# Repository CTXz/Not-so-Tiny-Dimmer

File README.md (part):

<!-- omit in toc -->
# Not-so-Tiny Dimmer 

What initaly just started as minimalist ATtiny based WS2812 LED strip dimmer, quickly turned into a cheap and feature rich ATtiny based WS2812 strip controller with single color, multi color and animation support. Non-addressable LED strips are also supported, but limited to single color features only.

## Contents
- [Contents](#contents)
- [Overview](#overview)
  - [Software](#software)
    - [Patches/Effects](#patcheseffects)
      - [`PATCH_SET_ALL`](#patchsetall)
      - [`PATCH_DISTRIBUTE`](#patchdistribute)
      - [`PATCH_ANIMATION_BREATHE_POT_CTRL`](#patchanimationbreathepotctrl)
      - [`PATCH_ANIMATION_BREATHE_RAND_POT_CTRL`](#patchanimationbreatherandpotctrl)
      - [`PATCH_ANIMATION_BREATHE_RAINBOW_POT_CTRL`](#patchanimationbreatherainbowpotctrl)
      - [`PATCH_ANIMATION_BREATHE_ARR_POT_CTRL`](#patchanimationbreathearrpotctrl)
      - [`PATCH_ANIMATION_RAINBOW`](#patchanimationrainbow)
      - [`PATCH_ANIMATION_RAINBOW_POT_CTRL`](#patchanimationrainbowpotctrl)
      - [`PATCH_ANIMATION_SWAP`](#patchanimationswap)
      - [`PATCH_ANIMATION_SWAP_POT_CTRL`](#patchanimationswappotctrl)
      - [`PATCH_ANIMATION_ROTATE_RAINBOW`](#patchanimationrotaterainbow)
      - [`PATCH_ANIMATION_RAIN`](#patchanimationrain)
      - [`PATCH_ANIMATION_RAIN_POT_CTRL`](#patchanimationrainpotctrl)
  - [Hardware](#hardware)
    - [Building](#building)
      - [Schematic](#schematic)
      - [PCBs](#pcbs)
        - [Showcase](#showcase)
        - [Ordering](#ordering)
        - [Soldering Tips](#soldering-tips)
      - [Perfboard](#perfboard)
      - [Showcase](#showcase-1)
- [Flashing the firmware](#flashing-the-firmware)
- [Credits](#credits)
- [Project log](#project-log)
- [License](#license)

## Overview

The Not-so-Tiny dimmer is a open source ATtiny Based WS2812 RGB strip controller that offers support for single and multi color lights, as well various animations. Alternatively, the controller can also be used to drive non-addressable LED strips, but is only limited to single color patches and animations. 

### Software

The controller offers a patch bank with up to 10 patches, where each patch slot can be hard-coded in the [configuration header](src/config.h) to something as simple as projecting a single color across the strip, all the way to projecting flashy rainbow animations. If less than 10 patches are desired, the `NUM_PATCHES` directive can be reduced in the [configuration header](src/config.h).

Non-addressable RGB strips are also supported by the firmware by changing the `STRIP_TYPE` configuration in the [configuration header](src/config.h) to `NON_ADDR`, but will limit the selection to single color patches. Whether a patch is supported on non-addressable strips is indicated in the comments of the [patch macro definitions](src/patch_macros.h). A [template configuration for non-addressable strips](src/config_templates/config_non-addressable.h) can be found in the [configuration_templates directory](src/config_templates/).

**Please note that the required amount of program flash rises with the number and complexity of patches. Thus, the use of an ATtiny25 is likely to only limited to a few single color patches.** For ATtiny25 based controllers, a [minimal configuration file template](src/config_templates/config_minimal.h) has been provided.

Due to the fact that patches are implemented C preprocessor directives, increasing the maximum number of patches requires addition of case statements in the [update_strip](https://github.com/CTXz/Tiny-Dimmer/blob/master/src/main.c#L193) function, along with a change of the `NUM_PATCHES` directive.

#### Patches/Effects

The following section lists all available patches that can be assigned to any of the 10 patch slots defined in the [configuration header](src/config.h):

##### `PATCH_SET_ALL`

Parameters:
|Type|Name|Description|
|----|----|-----------|
|`uint8_t`|R|Red value (0 - 255)|
|`uint8_t`|G|Green value (0 - 255)|
|`uint8_t`|B|Blue value (0 - 255)|

Description:

Sets the entire LED strip to one color. The brightness can be adjusted by the potentiometer.

Supported on non-addressable strips: Yes

Example:
```c
#define PATCH_0 PATCH_SET_ALL(255, 255, 255) // Fills strip with white
```

Showcase:

##### `PATCH_DISTRIBUTE`

Parameters:
|Type|Name|Description|
|----|----|-----------|
|`RGB_t[]`|RGB_ARR|An RGB_ARRAY() enclosed array of literal RGB arrays. Ex. `RGB_ARRAY({255, 255, 255}, {0, 1, 2}, ...)`|

Description:

Distributes the provided array of RGB values evenly accross the entire LED strip. The brightness can be adjusted by the potentiometer.

Supported on non-addressable strips: No

Example:

```c
// First strip half pink, second cyan
#define PATCH_0 PATCH_DISTRIBUTE ( \
        RGB_ARRAY (                \
                {10, 255, 202},    \
                {255, 20, 127}     \
        )                          \
)
```

Showcase:

##### `PATCH_ANIMATION_BREATHE_POT_CTRL`

Parameters:
|Type|Name|Description|
|----|----|-----------|
|`uint8_t`|R|Red value|
|`uint8_t`|G|Green value|
|`uint8_t`|B|Blue value|

Description:

"Breathes" the provided RGB value across the entire strip. The duration of a "breath" can be altered by the potentiometer.

Supported on non-addressable strips: Yes

Example:

```c
#define PATCH_0 PATCH_ANIMATION_BREATHE_POT_CTRL(255, 255, 255) // Breathes white color
```

Showcase:

##### `PATCH_ANIMATION_BREATHE_RAND_POT_CTRL`

Description:

"Breathes" random RGB values across the entire strip.
The duration of the "breath" can be altered by the potentiometer.
Due to the rather poor randomness of rand(), the outcomes tend
to be similar.

Supported on non-addressable strips: Yes

Example:
```c
#define PATCH_0 PATCH_ANIMATION_BREATHE_RAND_POT_CTRL
```

##### `PATCH_ANIMATION_BREATHE_RAINBOW_POT_CTRL`

Parameters:

|Type|Name|Description|
|----|----|-----------|
|`uint8_t`|RGB_STEP_SIZE|Color steps after every "breath". A greater step size means the color difference  between each breath becomes more noticeable.|

Description:
c
Gradiently "Breathes" trough the rgb spectrum. The duration of the "breath" can be altered by the potentiometer.

Supported on non-addressable strips: Yes

Example:
```c
#define PATCH_0 PATCH_ANIMATION_BREATHE_RAINBOW_POT_CTRL(10) // Breathes trough rainbow with 10 steps in color between each breath
```

##### `PATCH_ANIMATION_BREATHE_ARR_POT_CTRL`

Parameters:

|Type|Name|Description|
|----|----|-----------|
|`RGB_t[]`|RGB_ARR|An RGB_ARRAY() enclosed array of literal RGB arrays, ex. RGB_ARRAY({255, 255, 255}, {0, 1, 2}, ...)|

Description:

Gradiently "Breathes" trough the RGB array. The duration of the "breath" can be altered by the potentiometer.

Supported on non-addressable strips: Yes

Example:
```c
// Breathes trough red, green and blue
#define PATCH_0 PATCH_ANIMATION_BREATHE_ARR_POT_CTRL ( \
        RGB_ARRAY (                                    \
                {255, 0, 0},                           \
                {0, 255, 0},                           \
                {0, 0, 255}                            \
        )                                              \
)
```

##### `PATCH_ANIMATION_RAINBOW`

Parameters:

|Type|Name|Description|
|----|----|-----------|
|`uint8_t`|STEP_SIZE|Color steps (0 - 255) between each call. A greater value results in faster fading.|

Description:

Gradiently fades all LEDs simultaneously trough the RGB spectrum.

Supported on non-addressable strips: Yes

Example:
```c
#define PATCH_0 PATCH_ANIMATION_RAINBOW(10) // Fade trough RGB spectrum with 10 steps between each color change
```

Showcase:

##### `PATCH_ANIMATION_RAINBOW_POT_CTRL`

Description:

Gradiently fades all LEDs simultaneously trough the RGB spectrum.
The step size, and thus fade speed, can be altered by the potentiometer.

Supported on non-addressable strips: Yes

Example:

```c
#define PATCH_0 PATCH_ANIMATION_RAINBOW_POT_CTRL
```

##### `PATCH_ANIMATION_SWAP`

Parameters:

|Type|Name|Description|
|----|----|-----------|
|`uint8_t`|RFH|Red value of first strip half|
|`uint8_t`|GFH|Green value of first strip half|
|`uint8_t`|BFH|Blue value of first strip half|
|`uint8_t`|RFH|Red value of second strip half|
|`uint8_t`|GFH|Green value of second strip half|
|`uint8_t`|BFH|Blue value of second strip half|
|`unsigned long`|SWAP_TIME|Time (ms) after which the halves get swapped|

Description:

Splits the strip in two halves and continuously swaps their colors.

Supported on non-addressable strips: No

Example:
```c
#define PATCH_9 PATCH_ANIMATION_SWAP(255, 0, 0, 0, 0, 255, 1000) // Swaps between off and a random color
```

Showcase:

##### `PATCH_ANIMATION_SWAP_POT_CTRL`

Parameters:

|Type|Name|Description|
|----|----|-----------|
|`uint8_t`|RFH|Red value of first strip half|
|`uint8_t`|GFH|Green value of first strip half|
|`uint8_t`|BFH|Blue value of first strip half|
|`uint8_t`|RFH|Red value of second strip half|
|`uint8_t`|GFH|Green value of second strip half|
|`uint8_t`|BFH|Blue value of second strip half|

Description:

Splits the strip in two halves and continuously swaps their colors. The swap time can be altered by the potentiometer.

Supported on non-addressable strips: No

```c
#define PATCH_9 PATCH_ANIMATION_SWAP(255, 0, 0, 0, 0, 255) // Swaps between red and blue at a speed set by the potentiometer
```

##### `PATCH_ANIMATION_ROTATE_RAINBOW`

Parameters:

|Type|Name|Description|
|----|----|-----------|
|`uint8_t`|step_size|Color steps between each pixel|

Description:

Rotates the rgb spectrum across the strip.

Example:
```c
#define PATCH_0 PATCH_ANIMATION_ROTATE_RAINBOW(10)
```

Supported on non-addressable strips: No

Showcase:

##### `PATCH_ANIMATION_RAIN`

Parameters:

|Type|Name|Description|
|----|----|-----------|
|`uint8_t`|_R|Red color value|
|`uint8_t`|_G|Green color value|
|`uint8_t`|_B|Blue color value|
|`uint16_t`|MAX_DROPS|Maximum amount of visible "droplets" at a time|
|`uint16_t`|MIN_T_APPART|Minimum time in ms between drops|
|`uint16_t`|MAX_T_APPART|Maximum time in ms between drops|
|`uint8_t`|STEP_SIZE|Step size of droplet fading|

Description:

Creates a rain effect across the strip.
Note that this effect makes use of an RGB buffer and will linearly increase memory consumption with strip size.

Supported on non-addressable strips: No

Example:

```c
// White and cyan rain with max 10 drops, a minimum time of 0ms, maximum time of 100ms and step size of 10
#define PATCH_0 PATCH_ANIMATION_RAIN(255, 255, rand()%255, 10, 0, 100, 10)
```

Showcase:

##### `PATCH_ANIMATION_RAIN_POT_CTRL`

Parameters:

|Type|Name|Description|
|----|----|-----------|
|`uint8_t`|_R|Red color value|
|`uint8_t`|_G|Green color value|
|`uint8_t`|_B|Blue color value|

Description:

Creates a rain effect across the strip. The "intensity" of the rain can be adjusted with the potentiometer. Note that this effect makes use of an RGB buffer and will linearly increase memory consumption with strip size.

Supported on non-addressable strips: No

Example:

```c
// White and cyan rain with potentiometer intensity control
#define PATCH_0 PATCH_ANIMATION_RAIN(255, 255, rand()%255)
```

### Hardware

To navigate trough the patch bank, a single push button is provided. Once the last patch has been reached, the first patch is loaded again upon button press. Many patches also offer a tweakable parameter, such as brightness and speed control. A potentiometer is used to adjust these parameters in real time.

To compensate for sloppy hardware jobs, the firmware also offers potentiometer and push button noise reduction to reduce brightness flickering and false patch toggling. It should be noted however, that these features cost program flash and runtime cycles and can be adjusted or disabled in the [configuration header](src/config.h).

The controller firmware has been written for ATtiny85 chips, but will tightly fit onto a ATtiny25 chip if fewer and minimal patches are used. Unless the controller is planned to be used as a simple single-color WS2812 RGB dimmer, it is really recommended to at least use an ATiny45, preferably an ATiny85 if one wants make full use of all features.

#### Building

The schematics and PCB files, including the gerbers, for the WS2812 and non-addressable LED strips versions can be found here:

- [WS2812](kicad/Not-So-Tiny-Dimmer/)
- [Non-Addressable strips](kicad/Not-So-Tiny-Dimmer_Non-addr/)

Alternatively, one can also build the Tiny Dimmer on a perfboard. A perfboard layout diagram for the WS2812 version has been provided in the [perfboard section)(#Perfboard) bellow.

The following components are required to build a Not-so-Tiny dimmer for WS2812 strips:

|Component|Quantity|Description|
|---------|--------|-----------|
|WS2812 strip|1|The controller drives addressable WS2812 RGB strips.|
|ATtiny 85/45/25|1|The chip that runs the firmware, hence the name "Tiny" in the name. Although the firmware will barely fit on a ATtiny25, it is highly recommended to use an ATiny45 or ATiny85 if additional features are to be added to the software later.|
|10k - 100k resistor (0204 recommended)|1|Pulls up the reset pin to prevent random resets (Optional for extra stability, since the ATtiny already has an internal pull-up)|
|1k resistor (0204 recommended)|1|Optional, used, along wiht a 100nf cermaic cap, to reduce push button debouncing|
|10k **vertical** linear potentiometer ([example](https://tech.alpsalpine.com/prod/e/html/potentiometer/rotarypotentiometers/rk09k/rk09k_list.html))|1|Used to set the brightness. 10k linear pots are recommended, but any linear pot between 1k and 100k should do the job.|
|10uF Electrolytic Capacitor|1|Optional, but helps decoupling power supply noise.|
|100nF Ceramic Capacitor|2|Optional, used to decouple supply noise and reduce push button debouncing|
|6mm x 6mm x (7mm - 10mm) Tactile Push Button|1|Used to toggle between colors and to activate fading. A height of at least 7mm is recommended.|
|2.54mm Male/Female headers|1|SPI header to program the MCU.|
|2.54mm 3 Pin PCB screw terminal block|1|WS2812 connector.|
|DC Barrel Jack|1|5V Voltage supply input.|

For a non-addressable strip controller, the following parts are requried:

|Component|Quantity|Description|
|---------|--------|-----------|
|Non-Addressable RGB strip|1|The controller drives non addressable RGB strips.|
|ATtiny 85/45/25|1|The chip that runs the firmware, hence the name "Tiny" in the name. Although the firmware will barely fit on a ATtiny25, it is highly recommended to use an ATiny45 or ATiny85 if additional features are to be added to the software later.|
|10k - 100k resistor|1|Pulls up the reset pin to prevent random resets (Optional for extra stability, since the ATtiny already has an internal pull-up)|
|1k resistor|1|Optional, used, along wiht a 100nf cermaic cap, to reduce push button debouncing|
|10k **vertical** linear potentiometer ([example](https://tech.alpsalpine.com/prod/e/html/potentiometer/rotarypotentiometers/rk09k/rk09k_list.html))|1|Used to set the brightness. 10k linear pots are recommended, but any linear pot between 1k and 100k should do the job.|
|10uF Electrolytic Capacitor|1|Optional, but helps decoupling power supply noise.|
|100nF Ceramic Capacitor|2|Optional, used to decouple supply noise and reduce push button debouncing|
|6mm x 6mm x (7mm - 10mm) Tactile Push Button|1|Used to toggle between colors and to activate fading. A height of at least 7mm is recommended.|
|IRF630 N-MOS|3|Drives the 12V powered RGB strip. Most TO-220 N-MOSFETs with the same pinout will do.|
|2.54mm Male/Female headers|1|SPI header to program the MCU.|
|2.54mm 2 Pin PCB screw terminal block|2|12V, 5V and GND Voltage supply input.|
|2.54mm 4 Pin PCB screw terminal block|1|Non-Addressable strip connector.|

The controller can also be easily be built with a digispark board. 

The price for the components can range anywhere between 10 to 15 EUR, depending from where you purchase the components, and their quality.

##### Schematic

WS2812 Version: 

Non-Addressable strip version:

##### PCBs

WS2812 Version:

Non-Addressable strip version:

###### Showcase

PCB rev 1.0.0 (hence the few quirks) front showcase:

PCB rev 1.0.0 back showcase (pardon the solder flux):

###### Ordering

To order PCBs, simply send the gerber files (found under the `kicad/` directory) to your favorite PCB manufacturer. For my boards, I have chosen to order them from [JLCPCB](https://jlcpcb.com/?gclid=Cj0KCQjwncT1BRDhARIsAOQF9LkeNfO6bdbyJwIi-upbhMTT3J_9f7ANeXa-8HaEN9GSgqXFjCqWPz4aAvFlEALw_wcB).

###### Soldering Tips

Some tips when soldering the PCBs:

- The push button and potentiometer are soldered to the back side of the PCB. This is so that the PCB can be easily mounted onto a panel.
- Start with the small components (resistors, ceramic caps)
- Some vertical pots have too big mounting pins (pins on the side) for the PCB. Cutting the mounting pins short does the job.

##### Perfboard

Top view:

##### Showcase

Perfboard:

## Flashing the firmware

Flashing the firmware is possible even with the chips attached to the board. Hence it is recommended to solder an SPI header onto the board if you're planning to update the software and do not wish to open up the device for every firmware update.

To flash the firmware, an SPI programmer is required. Since I still have a few spare Arduino's lying around, I decided to use an Arduino Leonardo with the [Arduino ISP firmware](https://www.arduino.cc/en/tutorial/arduinoISP) installed to program the controller.

Programming via SPI with ArduinoISP:

Since the firmware has been written in [PlatformIO](https://platformio.org/), it is easiest to download the IDE, simply import the project and flash it from there.

Should your Not-so-Tiny dimmer not use an ATtiny85, you must change the `board` directive in the [PlatformIO configuration file](platformio.ini) to your ATtiny model.   

In addition to that, the [PlatformIO configuration file](platformio.ini) also expects a stk500v1 programmer (compatible with Arduino over ISP). If you are not programming the controller via an Arduino, you must change `upload_protocol` to the the corresponding programmer in the configuration file (See the [PlatformIO atemlavr documentation](https://docs.platformio.org/en/latest/platforms/atmelavr.html)).

Once everything is set in PlatformIO, make sure the parameters in the [configuration header](src/config.h) match your needs and simply click the upload button. The firmware should be flashed onto your controller in no time. 

If you're planning to flash the firmware without the PlatformIO IDE, **make sure to program the ATtiny's fuses for it to run at 16Mhz!**

## Credits

Big credits to @cpldcpu's [light_ws2812](https://github.com/cpldcpu/light_ws2812) library as plenty of hise code has been used to drive the WS2812 strip.

## Project log

The Tiny dimmer was built mostly out of necessity for a kitchen light and quarantine boredom. The choice of components was initially more or less a result of the limited number of spare parts that I had lying around at home. In particular, I had a digispark with an ATtiny25 soldered onto it, which I figured could suffice for a simple kitchen light.
Working with 2 KB of program flash and 128 B of RAM certainly came with its challenges. The tiny amount of program memory put the use of the Arduino library and the common NeoPixelBus library completely out of question and I was forced to write the code in pure AVR C.

To drive the WS2812 strip I decided to give [cpldcpu's light_ws2812](https://github.com/cpldcpu/light_ws2812) library a shot, which I had essentially stripped down to the `ws2812_sendarray_mask` function. Since my plan was to control all pixels of the strip simultaneously (yes, I'm aware I could've used non addressable strips for that, but WS2812 strips are all I have lying around... besides they just need one pin to be driven), I had to find a way to alter the `ws2812_sendarray_mask` function to no longer accept a pixel buffer, which wastes an enormous amount of RAM, but rather a RGB object which it would apply to all LEDs.

Easier said than done, as the function is incredibly time sensitive. That's the  reason as to why the `ws2812_sendarray_mask` function's main loop, which transmits the color data to the strip, has been written in AVR assembly (unfortunately a assembly languages that I'm still very unfamiliar with). Applying the slightest changes always ended up breaking the function, until I figured that the compiler optimization might be the reason behind that. Turns out, by turning the compiler optimization using the `#pragma GCC pop_options` macro, the main loop becomes allot less sensitive to changes. I haven't taken a look at the pulse time differences that arise with and without optimization enabled, but it might be something interesting to look into. Never the less, I was happy that I could finally control the WS2812 strip as desired, without blowing away the ATtinys 128 B of RAM, and thus I rewrote the `ws2812_send_array` function to `ws2812_set_all` which sets all pixels to a provided RGB value.

From here, implementing the firmware was rather straight forward. Initially I planned to assign the push button an INT0 interrupt. However, after implementing button hold detection and noise reduction, support for interrupts has been dropped in favour of a pure state polling implementation.

Adding the fade animation was a little tricky in that its maximum speed, provided its best resolution, was heavily limited by the speed of the `ws2812_set_all` function. Hence, for faster fading speeds, I was forced to increase the step size for the colors, meaning faster fading speeds come at the cost of smoothness/resolution.

All in all, this was a fun project to kill some quarantine time and most importantly, I'm more than happy with the way the result turned out and it was nice to put my AVR C skills to use again. Sure, I could've bought a cheap chinese LED strip controller, but where's the fun in that. This controller is all about open source and allows me to extend its features by reprogramming it. If I ever plan on discarding it, I can simply pop out and desolder all components are reuse them for another project.

--- Update ---

I have since reworked the software quite a bit. The ws2812 functions have been reduced to a set of 4 core functions, `ws2812_prep_tx()`, `ws2812_wait_rst()`, `ws2812_tx_byte()`, `ws2812_end_tx()`. With these functions I have then implemented a hardware abstraction layer in the [strip.c](src/strip.c) file, which defines various routines to control the LED strip. Patches have been completely reworked and are now defined in the [configuration header](src/config.h) using macros provided by the [patch_macros.h](src/patch_macros.h) header file. Using macros allows for very flexible patches that aren't limited to a single function or some sort of array of a specific data type. This made room for the easy implementation of animations.

--- Update ---

I think it's time to admit that this project is no longer a minimal dimmer, in fact, it has become quite the opposite and is turning into a feature bloated over-engineered ATtiny based WS2812 controller that, at least if the quarantine boredom won't end soon, will be connected, and will require connection, to the world wide web, feature the clunkiest most inaccurate and unnecessary voice control, feature incredibly water and dust sensitive touch controls and some form of AI or who knows what the future offers.

In all seriousness, except for the fact that I've now renamed the project to Not-so-Tiny dimmer, the device can now be more accurately considered a LED strip controller. While I personally do take large joy in adding and using the additional flashy animations, I've taken into account that we're starting to cross the RGB hell border in the eyes of many people, and have hence made sure that the software architecture is very flexible and allows one to take full control of which features and patches to be implemented. Hell, if desired, the controller software can be reduced to only support a single light setting along with brightness control.

## License

All code in this project is licensed by the GNU GPLv3 license and hardware is licensed by the [TAPR Open Hardware License](https://tapr.org/the-tapr-open-hardware-license/).

Both licenses require to provide a copy of the modified source code and/or hardware documentation for any derivative work.

GNU GPLv3
```
                    GNU GENERAL PUBLIC LICENSE
                       Version 3, 29 June 2007

 Copyright (C) 2007 Free Software Foundation, Inc. <https://fsf.org/>
 Everyone is permitted to copy and distribute verbatim copies
 of this license document, but changing it is not allowed.

                            Preamble

  The GNU General Public License is a free, copyleft license for
software and other kinds of works.

  The licenses for most software and other practical works are designed
to take away your freedom to share and change the works.  By contrast,
the GNU General Public License is intended to guarantee your freedom to
share and change all versions of a program--to make sure it remains free
software for all its users.  We, the Free Software Foundation, use the
GNU General Public License for most of our software; it applies also to
any other work released this way by its authors.  You can apply it to
your programs, too.

  When we speak of free software, we are referring to freedom, not
price.  Our General Public Licenses are designed to make sure that you
have the freedom to distribute copies of free software (and charge for
them if you wish), that you receive source code or can get it if you
want it, that you can change the software or use pieces of it in new
free programs, and that you know you can do these things.

  To protect your rights, we need to prevent others from denying you
these rights or asking you to surrender the rights.  Therefore, you have
certain responsibilities if you distribute copies of the software, or if
you modify it: responsibilities to respect the freedom of others.

  For example, if you distribute copies of such a program, whether
gratis or for a fee, you must pass on to the recipients the same
freedoms that you received.  You must make sure that they, too, receive
or can get the source code.  And you must show them these terms so they
know their rights.

  Developers that use the GNU GPL protect your rights with two steps:
(1) assert copyright on the software, and (2) offer you this License
giving you legal permission to copy, distribute and/or modify it.

  For the developers' and authors' protection, the GPL clearly explains
that there is no warranty for this free software.  For both users' and
authors' sake, the GPL requires that modified versions be marked as
changed, so that their problems will not be attributed erroneously to
authors of previous versions.

  Some devices are designed to deny users access to install or run
modified versions of the software inside them, although the manufacturer
can do so.  This is fundamentally incompatible with the aim of
protecting users' freedom to change the software.  The systematic
pattern of such abuse occurs in the area of products for individuals to
use, which is precisely where it is most unacceptable.  Therefore, we
have designed this version of the GPL to prohibit the practice for those
products.  If such problems arise substantially in other domains, we
stand ready to extend this provision to those domains in future versions
of the GPL, as needed to protect the freedom of users.

  Finally, every program is threatened constantly by software patents.
States should not allow patents to restrict development and use of
software on general-purpose computers, but in those that do, we wish to
avoid the special danger that patents applied to a free program could
make it effectively proprietary.  To prevent this, the GPL assures that
patents cannot be used to render the program non-free.

  The precise terms and conditions for copying, distribution and
modification follow.

                       TERMS AND CONDITIONS

  1. Definitions.

  "This License" refers to version 3 of the GNU General Public License.

  "Copyright" also means copyright-like laws that apply to other kinds of
works, such as semiconductor masks.

  "The Program" refers to any copyrightable work licensed under this
License.  Each licensee is addressed as "you".  "Licensees" and
"recipients" may be individuals or organizations.

  To "modify" a work means to copy from or adapt all or part of the work
in a fashion requiring copyright permission, other than the making of an
exact copy.  The resulting work is called a "modified version" of the
earlier work or a work "based on" the earlier work.

  A "covered work" means either the unmodified Program or a work based
on the Program.

  To "propagate" a work means to do anything with it that, without
permission, would make you directly or secondarily liable for
infringement under applicable copyright law, except executing it on a
computer or modifying a private copy.  Propagation includes copying,
distribution (with or without modification), making available to the
public, and in some countries other activities as well.

  To "convey" a work means any kind of propagation that enables other
parties to make or receive copies.  Mere interaction with a user through
a computer network, with no transfer of a copy, is not conveying.

  An interactive user interface displays "Appropriate Legal Notices"
to the extent that it includes a convenient and prominently visible
feature that (1) displays an appropriate copyright notice, and (2)
tells the user that there is no warranty for the work (except to the
extent that warranties are provided), that licensees may convey the
work under this License, and how to view a copy of this License.  If
the interface presents a list of user commands or options, such as a
menu, a prominent item in the list meets this criterion.

  1. Source Code.

  The "source code" for a work means the preferred form of the work
for making modifications to it.  "Object code" means any non-source
form of a work.

  A "Standard Interface" means an interface that either is an official
standard defined by a recognized standards body, or, in the case of
interfaces specified for a particular programming language, one that
is widely used among developers working in that language.

  The "System Libraries" of an executable work include anything, other
than the work as a whole, that (a) is included in the normal form of
packaging a Major Component, but which is not part of that Major
Component, and (b) serves only to enable use of the work with that
Major Component, or to implement a Standard Interface for which an
implementation is available to the public in source code form.  A
"Major Component", in this context, means a major essential component
(kernel, window system, and so on) of the specific operating system
(if any) on which the executable work runs, or a compiler used to
produce the work, or an object code interpreter used to run it.

  The "Corresponding Source" for a work in object code form means all
the source code needed to generate, install, and (for an executable
work) run the object code and to modify the work, including scripts to
control those activities.  However, it does not include the work's
System Libraries, or general-purpose tools or generally available free
programs which are used unmodified in performing those activities but
which are not part of the work.  For example, Corresponding Source
includes interface definition files associated with source files for
the work, and the source code for shared libraries and dynamically
linked subprograms that the work is specifically designed to require,
such as by intimate data communication or control flow between those
subprograms and other parts of the work.

  The Corresponding Source need not include anything that users
can regenerate automatically from other parts of the Corresponding
Source.

  The Corresponding Source for a work in source code form is that
same work.

  2. Basic Permissions.

  All rights granted under this License are granted for the term of
copyright on the Program, and are irrevocable provided the stated
conditions are met.  This License explicitly affirms your unlimited
permission to run the unmodified Program.  The output from running a
covered work is covered by this License only if the output, given its
content, constitutes a covered work.  This License acknowledges your
rights of fair use or other equivalent, as provided by copyright law.

  You may make, run and propagate covered works that you do not
convey, without conditions so long as your license otherwise remains
in force.  You may convey covered works to others for the sole purpose
of having them make modifications exclusively for you, or provide you
with facilities for running those works, provided that you comply with
the terms of this License in conveying all material for which you do
not control copyright.  Those thus making or running the covered works
for you must do so exclusively on your behalf, under your direction
and control, on terms that prohibit them from making any copies of
your copyrighted material outside their relationship with you.

  Conveying under any other circumstances is permitted solely under
the conditions stated below.  Sublicensing is not allowed; section 10
makes it unnecessary.

  3. Protecting Users' Legal Rights From Anti-Circumvention Law.

  No covered work shall be deemed part of an effective technological
measure under any applicable law fulfilling obligations under article
11 of the WIPO copyright treaty adopted on 20 December 1996, or
similar laws prohibiting or restricting circumvention of such
measures.

  When you convey a covered work, you waive any legal power to forbid
circumvention of technological measures to the extent such circumvention
is effected by exercising rights under this License with respect to
the covered work, and you disclaim any intention to limit operation or
modification of the work as a means of enforcing, against the work's
users, your or third parties' legal rights to forbid circumvention of
technological measures.

  4. Conveying Verbatim Copies.

  You may convey verbatim copies of the Program's source code as you
receive it, in any medium, provided that you conspicuously and
appropriately publish on each copy an appropriate copyright notice;
keep intact all notices stating that this License and any
non-permissive terms added in accord with section 7 apply to the code;
keep intact all notices of the absence of any warranty; and give all
recipients a copy of this License along with the Program.

  You may charge any price or no price for each copy that you convey,
and you may offer support or warranty protection for a fee.

  5. Conveying Modified Source Versions.

  You may convey a work based on the Program, or the modifications to
produce it from the Program, in the form of source code under the
terms of section 4, provided that you also meet all of these conditions:

    a) The work must carry prominent notices stating that you modified
    it, and giving a relevant date.

    b) The work must carry prominent notices stating that it is
    released under this License and any conditions added under section
    7.  This requirement modifies the requirement in section 4 to
    "keep intact all notices".

    c) You must license the entire work, as a whole, under this
    License to anyone who comes into possession of a copy.  This
    License will therefore apply, along with any applicable section 7
    additional terms, to the whole of the work, and all its parts,
    regardless of how they are packaged.  This License gives no
    permission to license the work in any other way, but it does not
    invalidate such permission if you have separately received it.

    d) If the work has interactive user interfaces, each must display
    Appropriate Legal Notices; however, if the Program has interactive
    interfaces that do not display Appropriate Legal Notices, your
    work need not make them do so.

  A compilation of a covered work with other separate and independent
works, which are not by their nature extensions of the covered work,
and which are not combined with it such as to form a larger program,
in or on a volume of a storage or distribution medium, is called an
"aggregate" if the compilation and its resulting copyright are not
used to limit the access or legal rights of the compilation's users
beyond what the individual works permit.  Inclusion of a covered work
in an aggregate does not cause this License to apply to the other
parts of the aggregate.

  6. Conveying Non-Source Forms.

  You may convey a covered work in object code form under the terms
of sections 4 and 5, provided that you also convey the
machine-readable Corresponding Source under the terms of this License,
in one of these ways:

    a) Convey the object code in, or embodied in, a physical product
    (including a physical distribution medium), accompanied by the
    Corresponding Source fixed on a durable physical medium
    customarily used for software interchange.

    b) Convey the object code in, or embodied in, a physical product
    (including a physical distribution medium), accompanied by a
    written offer, valid for at least three years and valid for as
    long as you offer spare parts or customer support for that product
    model, to give anyone who possesses the object code either (1) a
    copy of the Corresponding Source for all the software in the
    product that is covered by this License, on a durable physical
    medium customarily used for software interchange, for a price no
    more than your reasonable cost of physically performing this
    conveying of source, or (2) access to copy the
    Corresponding Source from a network server at no charge.

    c) Convey individual copies of the object code with a copy of the
    written offer to provide the Corresponding Source.  This
    alternative is allowed only occasionally and noncommercially, and
    only if you received the object code with such an offer, in accord
    with subsection 6b.

    d) Convey the object code by offering access from a designated
    place (gratis or for a charge), and offer equivalent access to the
    Corresponding Source in the same way through the same place at no
    further charge.  You need not require recipients to copy the
    Corresponding Source along with the object code.  If the place to
    copy the object code is a network server, the Corresponding Source
    may be on a different server (operated by you or a third party)
    that supports equivalent copying facilities, provided you maintain
    clear directions next to the object code saying where to find the
    Corresponding Source.  Regardless of what server hosts the
    Corresponding Source, you remain obligated to ensure that it is
    available for as long as needed to satisfy these requirements.

    e) Convey the object code using peer-to-peer transmission, provided
    you inform other peers where the object code and Corresponding
    Source of the work are being offered to the general public at no
    charge under subsection 6d.

  A separable portion of the object code, whose source code is excluded
from the Corresponding Source as a System Library, need not be
included in conveying the object code work.

  A "User Product" is either (1) a "consumer product", which means any
tangible personal property which is normally used for personal, family,
or household purposes, or (2) anything designed or sold for incorporation
into a dwelling.  In determining whether a product is a consumer product,
doubtful cases shall be resolved in favor of coverage.  For a particular
product received by a particular user, "normally used" refers to a
typical or common use of that class of product, regardless of the status
of the particular user or of the way in which the particular user
actually uses, or expects or is expected to use, the product.  A product
is a consumer product regardless of whether the product has substantial
commercial, industrial or non-consumer uses, unless such uses represent
the only significant mode of use of the product.

  "Installation Information" for a User Product means any methods,
procedures, authorization keys, or other information required to install
and execute modified versions of a covered work in that User Product from
a modified version of its Corresponding Source.  The information must
suffice to ensure that the continued functioning of the modified object
code is in no case prevented or interfered with solely because
modification has been made.

  If you convey an object code work under this section in, or with, or
specifically for use in, a User Product, and the conveying occurs as
part of a transaction in which the right of possession and use of the
User Product is transferred to the recipient in perpetuity or for a
fixed term (regardless of how the transaction is characterized), the
Corresponding Source conveyed under this section must be accompanied
by the Installation Information.  But this requirement does not apply
if neither you nor any third party retains the ability to install
modified object code on the User Product (for example, the work has
been installed in ROM).

  The requirement to provide Installation Information does not include a
requirement to continue to provide support service, warranty, or updates
for a work that has been modified or installed by the recipient, or for
the User Product in which it has been modified or installed.  Access to a
network may be denied when the modification itself materially and
adversely affects the operation of the network or violates the rules and
protocols for communication across the network.

  Corresponding Source conveyed, and Installation Information provided,
in accord with this section must be in a format that is publicly
documented (and with an implementation available to the public in
source code form), and must require no special password or key for
unpacking, reading or copying.

  7. Additional Terms.

  "Additional permissions" are terms that supplement the terms of this
License by making exceptions from one or more of its conditions.
Additional permissions that are applicable to the entire Program shall
be treated as though they were included in this License, to the extent
that they are valid under applicable law.  If additional permissions
apply only to part of the Program, that part may be used separately
under those permissions, but the entire Program remains governed by
this License without regard to the additional permissions.

  When you convey a copy of a covered work, you may at your option
remove any additional permissions from that copy, or from any part of
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
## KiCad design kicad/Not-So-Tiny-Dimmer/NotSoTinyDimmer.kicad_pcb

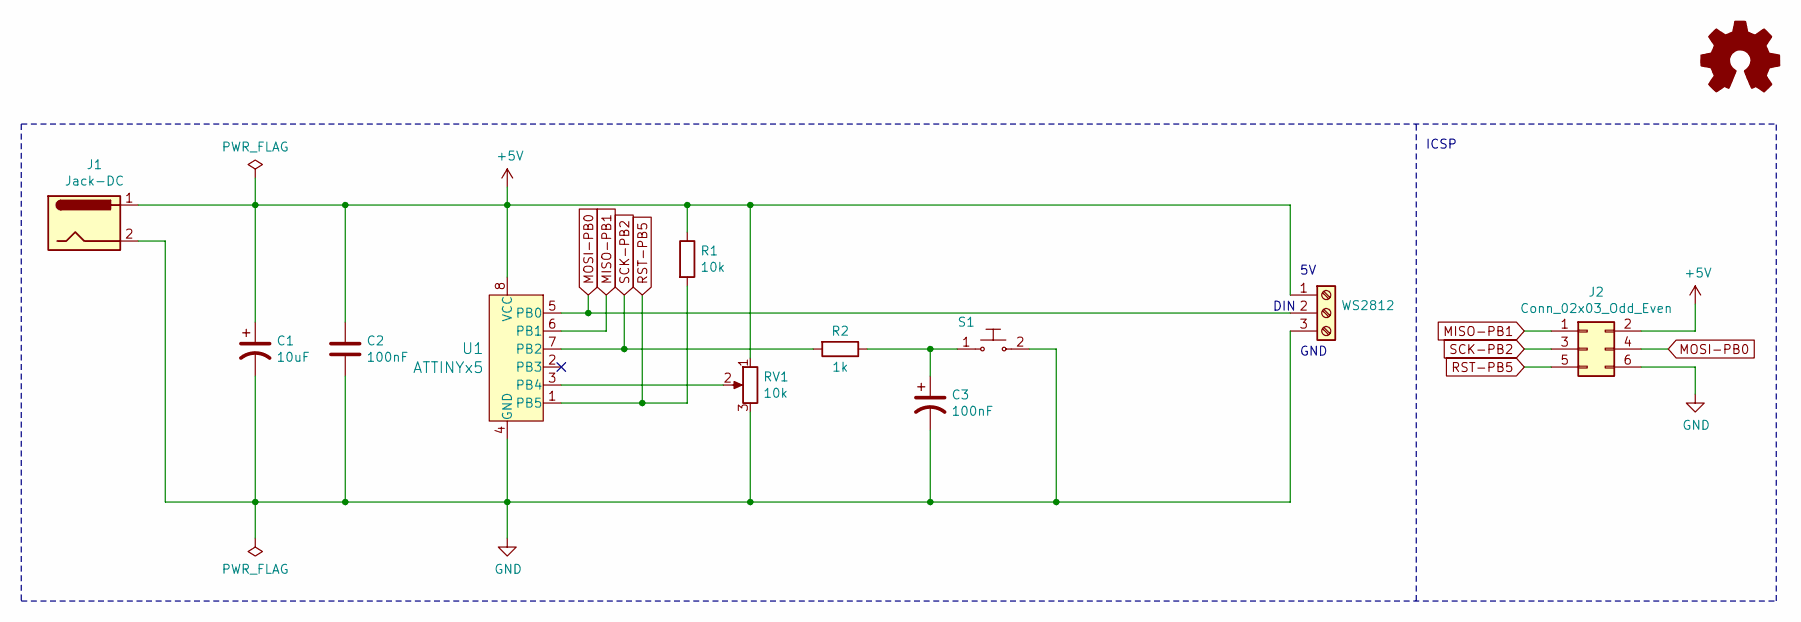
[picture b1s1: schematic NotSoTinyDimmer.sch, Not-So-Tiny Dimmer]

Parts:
C1: 10uF; CP_Radial_D5.0mm_P2.00mm
C2, C3: 100nF; C_Disc_D10.0mm_W2.5mm_P5.00mm
J1: Jack-DC; BarrelJack_Horizontal
J2: Conn_02x03_Odd_Even; PinHeader_2x03_P2.54mm_Vertical
R1: 10k; R_Axial_DIN0204_L3.6mm_D1.6mm_P5.08mm_Horizontal
R2: 1k; R_Axial_DIN0204_L3.6mm_D1.6mm_P5.08mm_Horizontal
RV1: 10k; Potentiometer_Alpha_RD901F-40-00D_Single_Vertical
S1: Push Button; SW_PUSH_6mm; MPN GPTS203211B; Digi-Key_PN CW181-ND
U1: ATTINYx5; DIP-8_W7.62mm; MPN ATTINY85-20PU; Digi-Key_PN ATTINY85-20PU-ND
WS2812: Screw_Terminal_01x03; TerminalBlock_TE_282834-3_1x03_P2.54mm_Horizontal

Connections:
+5V: C1.1, C2.1, J1.1, J2.2, R1.1, RV1.1, U1.8 (VCC), WS2812.1
GND: C1.2, C2.2, C3.2, J1.2, J2.6, RV1.3, S1.2, U1.4 (GND), WS2812.3
MISO-PB1: J2.1, U1.6 (PB1)
MOSI-PB0: J2.4, U1.5 (PB0), WS2812.2
unnamed: C3.1, R2.1, S1.1
unnamed: RV1.2, U1.3 (PB4)
RST-PB5: J2.5, R1.2, U1.1 (PB5)
SCK-PB2: J2.3, R2.2, U1.7 (PB2)

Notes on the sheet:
ICSP
GND
DIN

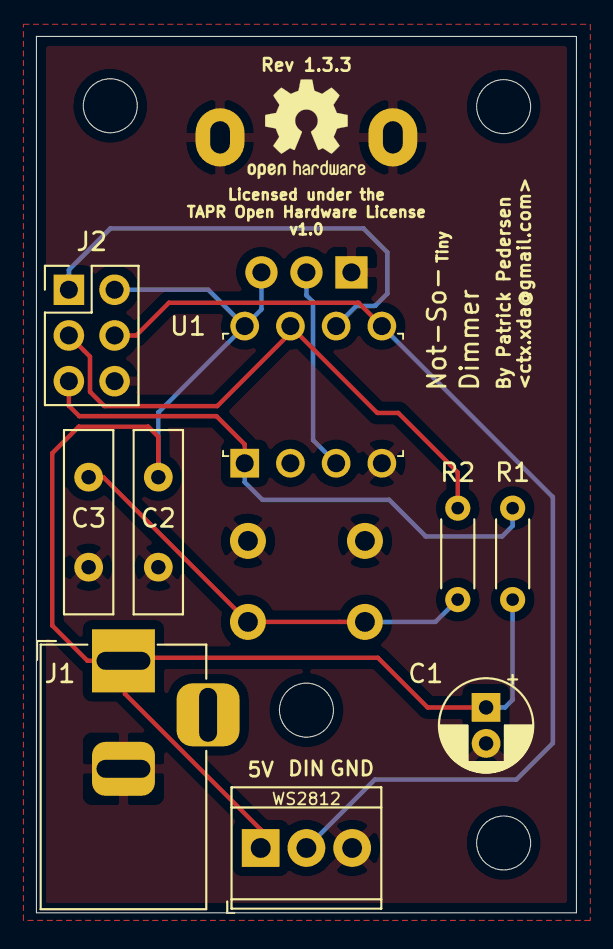
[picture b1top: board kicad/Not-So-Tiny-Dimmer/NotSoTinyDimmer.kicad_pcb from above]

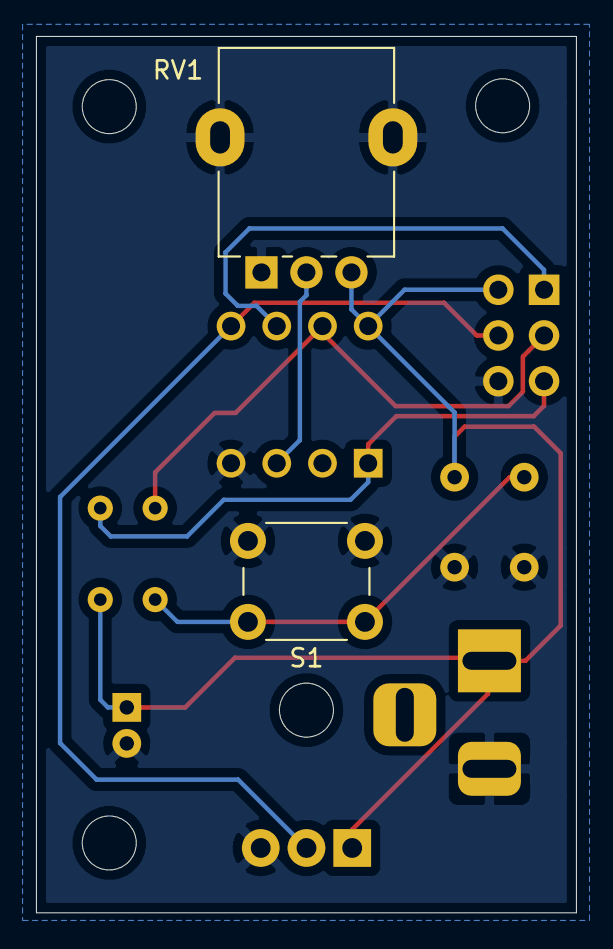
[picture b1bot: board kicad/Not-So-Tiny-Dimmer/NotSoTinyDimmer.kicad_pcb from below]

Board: 2 copper layers, 30.0 x 48.7 mm, 11 parts (2 on the bottom side), 8 nets.

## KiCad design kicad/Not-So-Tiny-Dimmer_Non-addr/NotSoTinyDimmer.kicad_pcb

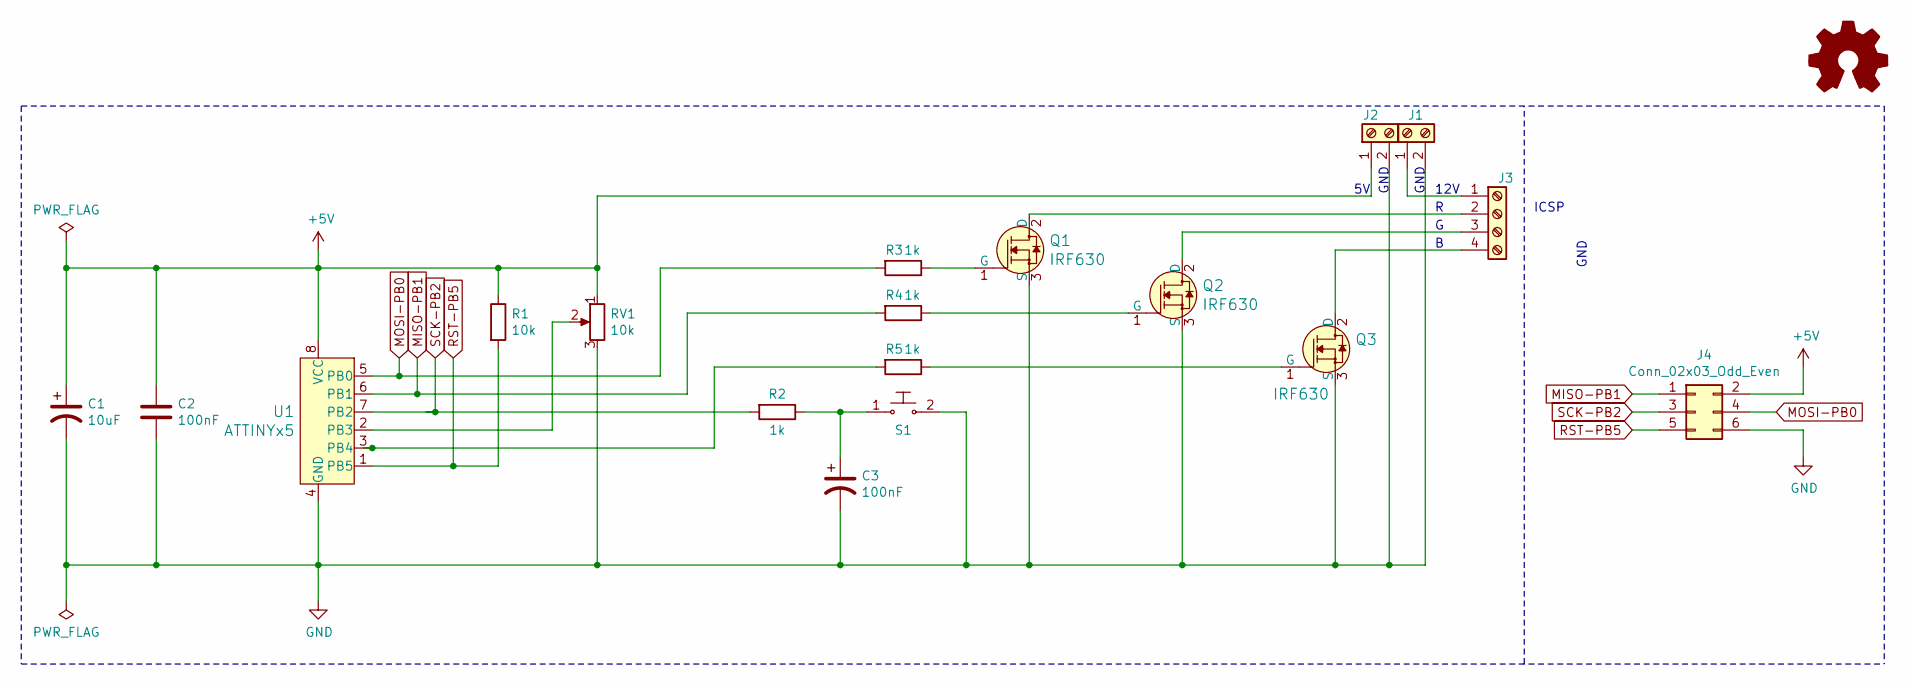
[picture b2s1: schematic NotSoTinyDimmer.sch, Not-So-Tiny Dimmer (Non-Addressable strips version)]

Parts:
C1: 10uF; CP_Radial_D5.0mm_P2.00mm
C2, C3: 100nF; C_Disc_D10.0mm_W2.5mm_P5.00mm
J1, J2: Screw_Terminal_01x02; TerminalBlock_TE_282834-2_1x02_P2.54mm_Horizontal
J3: Screw_Terminal_01x04; TerminalBlock_TE_282834-4_1x04_P2.54mm_Horizontal
J4: Conn_02x03_Odd_Even; PinHeader_2x03_P2.54mm_Vertical
Q1, Q2, Q3: IRF630; TO-220-3
R1: 10k; R_Axial_DIN0204_L3.6mm_D1.6mm_P5.08mm_Horizontal
R2, R3, R4, R5: 1k; R_Axial_DIN0204_L3.6mm_D1.6mm_P5.08mm_Horizontal
RV1: 10k; Potentiometer_Alpha_RD901F-40-00D_Single_Vertical
S1: Push Button; SW_PUSH_6mm; MPN GPTS203211B; Digi-Key_PN CW181-ND
U1: ATTINYx5; DIP-8_W7.62mm; MPN ATTINY85-20PU; Digi-Key_PN ATTINY85-20PU-ND

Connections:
+5V: C1.1, C2.1, J1.1, J4.2, R1.1, RV1.1, U1.8 (VCC)
GND: C1.2, C2.2, C3.2, J1.2, J2.2, J4.6, Q1.3 (S), Q2.3 (S), Q3.3 (S), RV1.3, S1.2, U1.4 (GND)
MISO-PB1: J4.1, R4.2, U1.6 (PB1)
MOSI-PB0: J4.4, R3.2, U1.5 (PB0)
unnamed: C3.1, R2.1, S1.1
unnamed: J2.1, J3.1
unnamed: J3.2, Q1.2 (D)
unnamed: J3.3, Q2.2 (D)
unnamed: J3.4, Q3.2 (D)
unnamed: Q1.1 (G), R3.1
unnamed: Q2.1 (G), R4.1
unnamed: Q3.1 (G), R5.1
unnamed: R5.2, U1.3 (PB4)
unnamed: RV1.2, U1.2 (PB3)
RST-PB5: J4.5, R1.2, U1.1 (PB5)
SCK-PB2: J4.3, R2.2, U1.7 (PB2)

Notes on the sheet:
ICSP
12V
GND

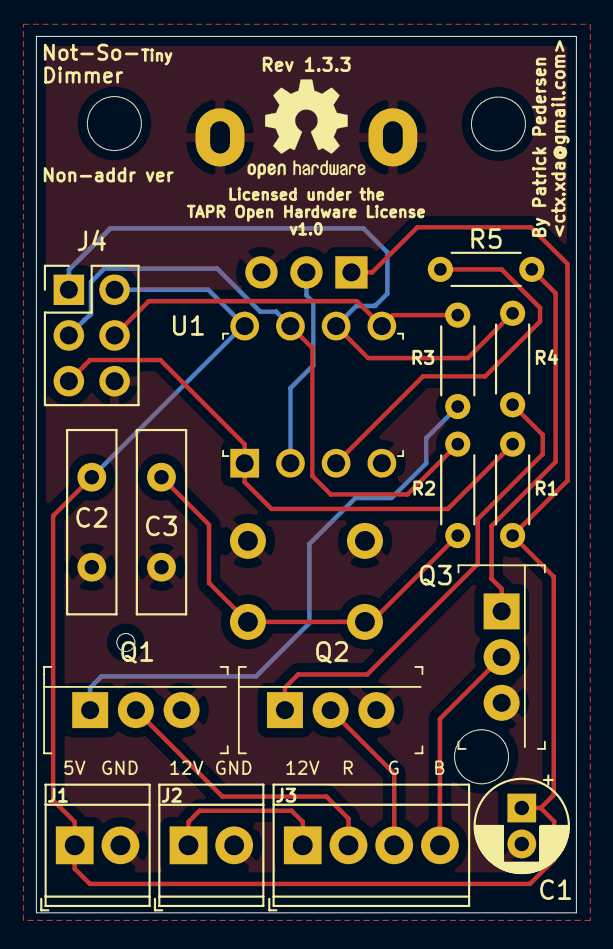
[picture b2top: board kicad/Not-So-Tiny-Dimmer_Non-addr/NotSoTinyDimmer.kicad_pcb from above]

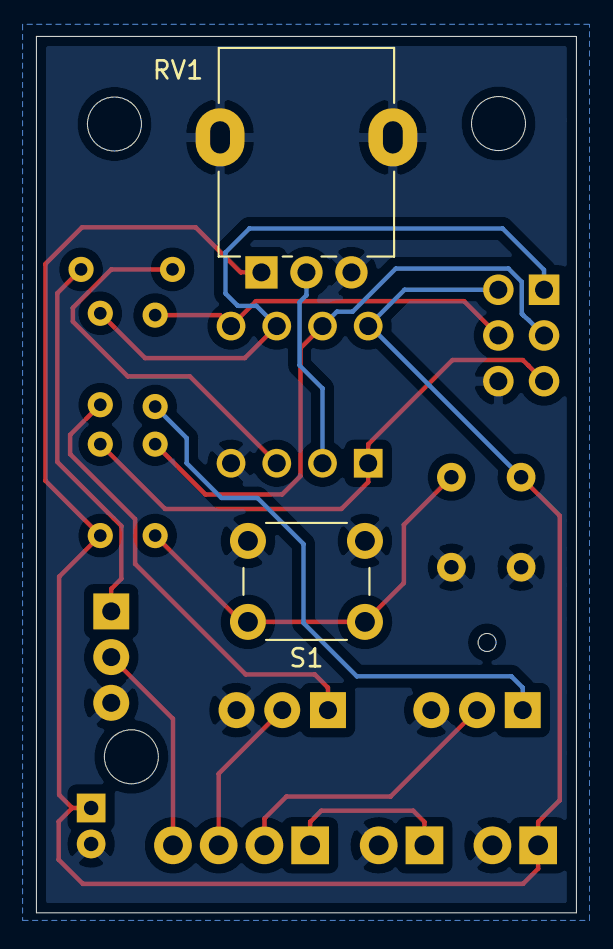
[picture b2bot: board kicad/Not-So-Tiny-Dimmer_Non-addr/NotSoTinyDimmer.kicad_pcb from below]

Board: 2 copper layers, 30.0 x 48.7 mm, 18 parts (2 on the bottom side), 16 nets.

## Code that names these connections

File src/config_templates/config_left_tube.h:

  /*
   * Copyright (C) 2020  Patrick Pedersen

   * This program is free software: you can redistribute it and/or modify
   * it under the terms of the GNU General Public License as published by
   * the Free Software Foundation, either version 3 of the License, or
   * (at your option) any later version.

   * This program is distributed in the hope that it will be useful,
   * but WITHOUT ANY WARRANTY; without even the implied warranty of
   * MERCHANTABILITY or FITNESS FOR A PARTICULAR PURPOSE.  See the
   * GNU General Public License for more details.

   * You should have received a copy of the GNU General Public License
   * along with this program.  If not, see <https://www.gnu.org/licenses/>.
   * 
   * Author: Patrick Pedersen <ctx.xda@gmail.com>
   * Description: Configuration file for the Not-so-Tiny dimmer firmware.
   * 
   */

#include <stdlib.h>

#include "conifg_enums.h"

#include "ws2812.h"
#include "strip.h"
#include "patch_macros.h"

//////////////////////////////
// Non-Addressable RGB Strip
//////////////////////////////

// #define STRIP_TYPE NON_ADDR

// #define NON_ADDR_STRIP_R PB0 // Red LED pin (must support PWM)
// #define NON_ADDR_STRIP_G PB1 // Green LED pin (must support PWM)
// #define NON_ADDR_STRIP_B PB4 // Blue LED pin (must support PWM)

//////////////////////////////
// WS2812
//////////////////////////////

#define STRIP_TYPE WS2812

#define WS2812_DIN PB0                          // WS2812 DIN pin
#define WS2812_DIN_PORT PORTB                   // WS2812 DIN pin bank
#define WS2812_COLOR_ORDER GRB                  // Order in which color should be parsed to the strip (Most WS2812 strips use BGR)
#define WS2812_RESET_TIME  50                   // Time required for the WS2812 to reset
                                                // If runtime between strip writes exceeds the 
                                                // necessary reset time, this may be set to 0

//////////////////////////////
// Potentiometer
//////////////////////////////

#define BRIGHTNESS_POT_ADMUX_MSK (1 << MUX1)               // PB4 (Refer to table 17-4 in the ATtiny25/45/85 datasheet)

#define INVERT_POT                                         // Uncomment if pot is inverted

// #define ADC_AVG_SAMPLES XX                                 // Max 255 - Number of samples used to determine the average potentiometer value.
                                                              // Increase this if the LED strip is noisy, especially at lower settings.
                                                              // Higher values will reserve more runtime
                                                              // Set to <= 1 or comment out to disable

// #define POT_LOWER_BOUND XX                                 // Max 255 - Any potentiometer value lower or equal to the lower bound will be registered as 0
                                                              // Set to 0 or comment out to disable

// #define POT_UPPER_BOUND XX                                 // Max 255 - Any potentiometer value lower or equal to the lower bound will be registered as 255 

//////////////////////////////
// Push Button
//////////////////////////////

#define BTN PB2                                                // Push button pin

#define BTN_DEBOUNCE_TIME 10                                   // ms - Time to wait for button to debounce. Increasing this will reduce false trigger due to
                                                               // bouncing, but add a slight delay to color toggling.
                                                               // Set to 0 or comment out to disable

//////////////////////////////
// GATE
//////////////////////////////

#define GATE PB3

////////////////////////
// Patches
////////////////////////

// For a list of available patches, please refer to the
// patch_macros.h header
#define STRIP_SIZE 68
#define HALF STRIP_SIZE/2

#define NUM_PATCHES 18 // Max 10 (To increase, add cases to update_strip() in main.c)

#define PATCH_0 PATCH_DIAL_RGB(255)

// Red
#define PATCH_1 PATCH_SET_ALL(255, 0, 0)

// White
#define PATCH_2 PATCH_SET_ALL(255, 255, 255)

// Orange
#define PATCH_3 PATCH_SET_ALL(255, 25, 0)

// Jungle green
#define PATCH_4 PATCH_SET_ALL(50, 255, 50)

// Lime green
#define PATCH_5 PATCH_SET_ALL(206, 255, 20)

// Rosy pink
#define PATCH_6 PATCH_SET_ALL(255, 75, 75)

// Purple
#define PATCH_7 PATCH_SET_ALL(151, 0, 255)

// First strip half purple, second beige
#define PATCH_8 PATCH_SPLIT (255, 74,  33, 151, 0, 255, HALF)

// First strip second beige, half purple
#define PATCH_9 PATCH_SPLIT (151, 0, 255, 255, 74,  33, HALF)

// // Arizona
#define PATCH_10 PATCH_SPLIT (255, 75, 75, 126, 200, 69, HALF)

#define PATCH_11 PATCH_SPLIT (126, 200, 69, 255, 75, 75, HALF)

// // Peach blossom
#define PATCH_12 PATCH_SPLIT (200, 59, 44, 100, 150, 20, HALF)

#define PATCH_13 PATCH_SPLIT (100, 150, 20, 200, 59, 44, HALF)

// Gold Cyan
#define PATCH_14 PATCH_SPLIT (19, 150, 56, 255, 100, 0, HALF)

#define PATCH_15 PATCH_SPLIT (255, 100, 0, 19, 150, 56, HALF)

#define PATCH_16 PATCH_ANIMATION_ROTATE_RAINBOW_POT_CTRL(5)

#define PATCH_17 PATCH_ANIMATION_RAINBOW_POT_CTRL

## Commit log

2020-03-29 Added comments
2020-03-29 Main: Added RGB struct
2020-03-29 Added RGB struct + Modified ws2812_sendarray_mask to ws2812_set_all
2020-03-29 Fixed brightness
2020-03-30 Platformio: Compile for Attiny85
2020-03-31 Added fritzing sketch
2020-03-31 Added ADC averaging and lower bound for less flicker
2020-03-31 Config: Reduced ADC averaging sample size to 50
2020-03-31 Main: Added comments to newly added pot functions
2020-03-31 Removed TUDO Makerspace from copyright header
2020-03-31 Config: Use 255 samples for averaging
2020-04-01 Fade: Added debouncing on button release
2020-04-01 Set reset time and fade delay to 0 as runtime is already slow enough
2020-04-02 Fade: Added multiple fade frequencies
2020-04-02 Added btn_min_reads to reduce false release positives when holding down noisy buttons
2020-04-02 Config: Removed obsolete comment
2020-04-02 Boot: Added 10ms delay to allow supply voltage to calm down
2020-04-03 Added docs
2020-04-03 README: Added TOC
2020-04-03 README: Spelling
2020-04-03 Main: Do not indent directives
2020-04-03 Main: Removed unecessary directives
2020-04-03 Moved patches into config header
2020-04-03 Moved and renamed light_ws2812 to ws2812
2020-04-03 WS2812: Dropped ws2812_PORTREG and ws2812_DDRREG
2020-04-03 Implemented RGBA struct
2020-04-04 Added support for substrips
2020-04-04 Seperate between full patches and strip patches
2020-04-04 Main: Dropped set_ws2812
2020-04-05 WS2812: Implemeted ws2812_prep_tx, ws2812_wait_rst and ws2812_end_tx
2020-04-05 Seperated WS2812 core driver routines from abstract strip routines
2020-04-05 Strip: Include config file in strip header
2020-04-05 Major patches rework
    Patches are no longer stored in an array but defined as macros. This provides the
    innormous advantage of being able to flexibly make every patch unique.
    Setting patches is now done via patch macros, such as PATCH_SET_ALL, which sets
    the entire strip to a single color, PATCH_DISTRIBUTE, which distributes
    RGB array litterals evenly accross the LED strip and some animations.
    As part of this change, the strip_distribute_rgb and strip_fade_rgb functions
2020-04-05 Strip: rgb_apply_brightness: Do not apply brightness at 100%
2020-04-05 Strip: Set fade step size to 1 if step_size is 0
2020-04-05 Strip: Added strip_set_pxbuf
2020-04-05 Strip: Keep brightness independant from setters to save memory
2020-04-05 Strip: Embedded strip size into strip functions
2020-04-05 Added global rgb and pixel buffer object to save memory
    For functions that need to store to a rgb or pixel buffer object, creating a
    new static rgb, and especially pixel buffer object is a wasteful use of memory.
    Since at no time will two different routines have to access a rgb or pixelbuffer
    object, a single global rgb and pixel buffer object will suffice.
    The pixel buffer object MUST be tested for initialization, and if required, be
    initialized, by every function that wishes to make use of it. This is
2020-04-05 Dropped glob_rgb object
2020-04-06 Added breath animations
2020-04-06 Config: Fixed space after backslash
2020-04-06 Renamed pixel_buffer to pxbuf
2020-04-06 Renamed substrip to substrp
2020-04-08 Renamed structs
2020-04-09 Added strip_rotate_rgb_fade effect
2020-04-09 Renamed rgb fade to rainbow
2020-04-09 breath -> breathe
2020-04-09 strip_set* -> strip_apply*
2020-04-09 README: Added gif for showcase
2020-04-09 Renamed TinyDimmer directory to kicad
2020-04-09 Updated README and project name
2020-04-09 README: Added credits and license
2020-04-09 README: Minor changes
2020-04-09 Strip: Renamed strip_cpy and strip_free to substrp_cpy and substrp_free
2020-04-09 Strip: Added pixl struct
2020-04-09 Dropped init_RGBbuf
2020-04-09 Strip: Added strip_apply_pxbuf, moved glob_RGBbuf to strip.c and fixed RGBbuf type
2020-04-09 Strip: Initialize glob_RGBbuf with calloc to keep it empty after initialization
2020-04-09 Strip: Added zero_RGBbuf
2020-04-10 Added rain animation
2020-04-10 Added comments to rain effect functions
2020-04-10 Added minimal config template for T25 based controllers
2020-04-12 Added support for non-addressable RGB strips
2020-04-16 Added INVERT_POT
2020-04-16 Updated documentation
2020-04-16 README: Dropped code blocks for patch descriptions
2020-04-17 Pot inverterting: Invert value instead of subtracting with 255
2020-04-18 Patches: Added step size to rotate rainbow
2020-04-19 Strip: Make rotate_rainbow inline
2020-04-20 Strip: Added strip_override effect
2020-04-20 Strip: Take overflow fully into account during RGB fading
2020-04-20 Strip: Added delay parameter to rainbow effect
2020-04-21 ADC: Fixed adc not restoring auto-trigger mode
2020-04-24 Patch Macros: Updated rainbow patch macro to recent changes
2020-04-24 Strip: Added pxbuf struct + rain animation and strip_apply_pxbuf reworked to use less mem
    The pxbuf struct has been added which stores a dynamic buffer of pixel objects, allong with a size. To
    use the pixel buffer, pxbuf_init, pxbuf_insert, pxbuf_remove and pxbuf_remove_at functions have been added
    which ensure pixels are inserted and removed without breaking the order of pixels.
    The rain animation, and more specifically, the strip_apply_pxbuf function has now been modified to no longer map pixel buffers onto a potentially very large RGB buffer,
    but rather make use of the pixel buffer directly. This could potentially save allot of memory, and hopefully allows the use of the rain animation o
2020-04-24 Config: Updated config
2020-04-24 Patch macros: Updated parameters for pot controlled rain animation
2020-04-25 Added rgb_cpy
2020-04-26 README: Update
2020-04-27 Strip: reworked fading and updated comments
2020-05-01 Strip HAL: Updated comments
2020-05-01 Patch macros: Increased min time for rain and swap effects
2020-05-01 Strip HAL: Fixed RGB fading + Added pot ctrl for rotating rainbow effect
2020-05-01 Strip HAL: Replaced step_size parameter with delay + Updated rain patch
2020-05-04 Buttons: Dropped BTN_MIN_READS
2020-05-05 README: Updated schematic and list of parts
2020-05-05 Config: Updated config to PCB rev 1.3.x or lower
2020-05-05 README: Renamed Patches section to Patches/Effects
2020-05-05 Added PCB/Schematic files
2020-05-05 README: Minor fixes
2020-05-05 README: Increased res of PCB showcase
2020-05-31 Added rgb scroll effect
2020-09-17 Strip: Added descriptions of data structures
2020-09-17 Configs: Increased WS2812 reset time to 35ms
2020-09-19 Strip: Added calibration mode for dynamic determination of strip size
2020-09-19 Config: Increased reset time to 50us
2020-09-20 Strip: Calibration: Set endpoint initially at start
2020-10-04 Patches: Added PATCH_SPLIT
2020-10-04 Input: Added pot_avg
2020-10-04 Strip: Use pot_avg for calibration
2020-10-04 Patches: Use averaging on PATCH_RGB_POT_CTRL
2020-10-05 Reverted last commit
2020-10-05 Ported to C++
    Since it is planned to port the firmware to Arduino compatible boards, the
    code had to be ported to C++ in order to be compatible with the Arduino
    library. In the future the code will likely still remain C compatible
    for other platforms than Arduino.
2020-10-05 Added compatiblity to ATmega328(p)
    The firmware may now also be compiled for the ATmega328(p), meaning that
    ATmega328 based Arduino boards may now run the firmware.
    To compile for ATmega328 boards, use the config_atmega328.h configuration template
    and set the default_envs variable in platformio.ini to ATmega328P
2020-10-16 Config: Updated default config to work with C++
2020-10-18 Added Arduino compatibility
    The firmware has been ported to the Arduino framework and may now be easily falshed onto any AVR
    based Arduino (Uno, nano, micro, leonardo) or Arduino clone board. Non-AVR arduino compatible
    boards are still not supported by the firmware, as it relies on the AVR EEPROM library
    and the light WS2812 driver, which has been explicitly written for AVR chips. Fortunately,
    porting the firmware to devices which support the Arduino framework should now a great deal simpler!
2020-10-20 Added CV support
    The firmware now supports control voltage support, allowing one to control lights and animations trough an external 0-5V voltage signal.
    This may be used to sync effects with an external beat detection circuit, a motion detection circuit, perhaps a modular synthesizer (provided
    the voltages have been scaled correctly), a light detection circuit, a wifi chip, etc. the possibilies are limitless.
    Since the ADC now no longer only uses one, but two channels, "ghosting" could occur when switching the
    ADC mux quickly on free-running/auto-trigger mode. Hence, for native AVR builds, support for auto-trigger
    mode had to be dropped in favour of single shot mode.
2020-10-30 Strip: Added fading animations
2020-11-19 Platformio: Specify port for attiny
2020-12-14 Strip: Calibration: Do not update strip while button is being held
    Updating the strip while the button is being held messes with the time functions
2020-12-14 Config: Added BRIGHTNESS_POT_MISSING flags for controllers without a potentiometer
2021-01-26 Main: Only pinMode brightness pot if not missing
2021-01-26 Config: Strip: Added STRIP_SIZE config for hard-coded strip sizes
2021-11-05 Initial commit for Sy's controller
2021-11-05 Added 5V gate input
2022-03-27 Intial commit for TUDO branch
2022-03-27 Config: Fixed strip size for right tube config
2022-03-28 Config: Updated to new LED controller
2022-03-29 Config for unit P1
2022-03-30 Initial commit for P2
2022-04-09 Config: Replaced pot, inversion no longer required
2022-04-10 Initial commit for B1
2022-04-30 Initial commit for shot tray

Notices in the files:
README.md:
License:
All code in this project is licensed by the GNU GPLv3 license and hardware is licensed by the [TAPR Open Hardware License](https://tapr.org/the-tapr-open-hardware-license/).
Both licenses require to provide a copy of the modified source code and/or hardware documentation for any derivative work.
GNU GPLv3
Version 3, 29 June 2007
Copyright (C) 2007 Free Software Foundation, Inc.
Everyone is permitted to copy and distribute verbatim copies
of this license document, but changing it is not allowed.
The GNU General Public License is a free, copyleft license for
